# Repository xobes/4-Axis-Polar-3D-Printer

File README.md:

# 4 Axis Polar 3D Printer

This is my 4 axis, polar, "core-RΘ" 3D printer – an entirely new type of multi axis 3D printer designed from the ground up. 

Check out my [youtube video](https://www.youtube.com/watch?v=VEgwnhLHy3g) to see it in action!

### Slicer
A multi axis printer is pretty hopeless without a non-planar slicer, which is why I built this quick [radial slicer](https://github.com/jyjblrd/Radial_Non_Planar_Slicer) for the printer. This leverages the printer's rotating nozzle to print simple parts without supports, but there are some limitations to it which I cover in the YouTube video. I'm also working on an optimization based slicer which will be able to print any object without support so stay tuned for that!

### Assembly
You can view the [3d model online](https://a360.co/3VdXkRY) to see how to assemble the printer. Everything is 3D printable, however I got the extruder mount made out of metal by JLCPCB as there is quite a bit of torque on that part. I've also included the gerber files to make your own PCB buildplate, but a sheet of MDF wood would also work.

### BOM
Some links are included so you know what to get, but they are by no means the best source to get the parts.
|                          | Qty |                                                                                                                                                                                                                                                                                                                                                                                                                                | Note            |
| ------------------------ | --- | ------------------------------------------------------------------------------------------------------------------------------------------------------------------------------------------------------------------------------------------------------------------------------------------------------------------------------------------------------------------------------------------------------------------------------ | --------------- |
| Frame                    |     |                                                                                                                                                                                                                                                                                                                                                                                                                                |                 |
| 2040 Extrusion 350mm     | 1   | [Aliexpress](https://www.aliexpress.us/item/1005005037443914.html?pdp_npi=4%40dis%21USD%21US%20%244.70%21US%20%242.87%21%21%214.70%212.87%21%402101585f17218160977374631e6f09%2112000031411902085%21sh%21HK%213408833611%21X&spm=a2g0o.store_pc_allItems_or_groupList.new_all_items_2007532827729.1005005037443914&gatewayAdapt=glo2usa)                                                                                             |                 |
| 2040 Extrusion 100mm     | 1   | [Aliexpress](https://www.aliexpress.us/item/1005005037443914.html?pdp_npi=4%40dis%21USD%21US%20%244.70%21US%20%242.87%21%21%214.70%212.87%21%402101585f17218160977374631e6f09%2112000031411902085%21sh%21HK%213408833611%21X&spm=a2g0o.store_pc_allItems_or_groupList.new_all_items_2007532827729.1005005037443914&gatewayAdapt=glo2usa)                                                                                             |                 |
| 2020 Extrusion 150mm     | 1   | [Aliexpress](https://www.aliexpress.us/item/1005005037443914.html?pdp_npi=4%40dis%21USD%21US%20%244.70%21US%20%242.87%21%21%214.70%212.87%21%402101585f17218160977374631e6f09%2112000031411902085%21sh%21HK%213408833611%21X&spm=a2g0o.store_pc_allItems_or_groupList.new_all_items_2007532827729.1005005037443914&gatewayAdapt=glo2usa)                                                                                             |                 |
| 2020 Extrusion 250mm     | 1   | [Aliexpress](https://www.aliexpress.us/item/1005005037443914.html?pdp_npi=4%40dis%21USD%21US%20%244.70%21US%20%242.87%21%21%214.70%212.87%21%402101585f17218160977374631e6f09%2112000031411902085%21sh%21HK%213408833611%21X&spm=a2g0o.store_pc_allItems_or_groupList.new_all_items_2007532827729.1005005037443914&gatewayAdapt=glo2usa)                                                                                             |                 |
| 2020 corner bracket      | 10  | [Aliexpress](https://www.aliexpress.us/item/1005002883833150.html?pdp_npi=4%40dis%21USD%21US%20%248.00%21US%20%245.36%21%21%218.00%215.36%21%402101585f17218162290038619e6f09%2112000022608302408%21sh%21HK%213408833611%21X&spm=a2g0o.store_pc_allItems_or_groupList.new_all_items_2007532827729.1005002883833150&gatewayAdapt=glo2usa)                                                                                             |                 |
|                          |     |                                                                                                                                                                                                                                                                                                                                                                                                                                |                 |
| Hardware                 |     |                                                                                                                                                                                                                                                                                                                                                                                                                                |                 |
| 2020 T Nuts              | 50  | [Aliexpress](https://aliexpress.us/item/1005003023734101.html?pdp_npi=4%40dis%21USD%21US%20%243.50%21US%20%242.27%21%21%213.50%212.27%21%402101585f17218164046887395e6f09%2112000023289976894%21sh%21HK%213408833611%21X&spm=a2g0o.store_pc_allItems_or_groupList.new_all_items_2007532827729.1005003023734101&gatewayAdapt=glo2usa)                                                                                                 |                 |
| MGN9 250mm Rail          | 1   | [Aliexpress](https://www.aliexpress.us/item/1005004908405311.html?spm=a2g0o.detail.0.0.3bb48SF18SF1v1&mp=1&gatewayAdapt=glo2usa)                                                                                                                                                                                                                                                                                                     |                 |
| MGN12 250mm Rail         | 2   | [Aliexpress](https://www.aliexpress.us/item/1005004908405311.html?spm=a2g0o.detail.0.0.3bb48SF18SF1v1&mp=1&gatewayAdapt=glo2usa)                                                                                                                                                                                                                                                                                                     |                 |
| MGN9C Block              | 2   | [Aliexpress](https://www.aliexpress.us/item/1005004908405311.html?spm=a2g0o.detail.0.0.3bb48SF18SF1v1&mp=1&gatewayAdapt=glo2usa)                                                                                                                                                                                                                                                                                                     |                 |
| MGN12H Block             | 2   | [Aliexpress](https://www.aliexpress.us/item/1005004908405311.html?spm=a2g0o.detail.0.0.3bb48SF18SF1v1&mp=1&gatewayAdapt=glo2usa)                                                                                                                                                                                                                                                                                                     |                 |
| M4 Screw Set             |     | [Aliexpress](https://www.aliexpress.us/item/1005002109863123.html?spm=a2g0o.productlist.main.17.7fe82c812tBHeu&algo_pvid=9b3adcc2-eaa7-49f5-827b-65c76ebec4ab&algo_exp_id=9b3adcc2-eaa7-49f5-827b-65c76ebec4ab-8&pdp_npi=4%40dis%21USD%2114.98%218.24%21%21%2114.98%218.24%21%402101364217218106530737554e0d29%2112000018775202479%21sea%21HK%213408833611%21&curPageLogUid=3mmH5TGniEUf&utparam-url=scene%3Asearch%7Cquery_from%3A) |                 |
| M3 Screw Set             |     |                                                                                                                                                                                                                                                                                                                                                                                                                                | Need 40mm screw |
| M3 Square Nut            | 50  | [Aliexpress](https://www.aliexpress.us/item/1005001612157787.html?spm=a2g0o.productlist.main.1.5d017e8aeZHkcO&algo_pvid=3c10a105-0205-4d35-910a-e991c6a990df&algo_exp_id=3c10a105-0205-4d35-910a-e991c6a990df-0&pdp_npi=4%40dis%21USD%212.68%212.28%21%21%212.68%212.28%21%402102f6cb17218121155956718ec6aa%2112000028150283667%21sea%21HK%213408833611%21&curPageLogUid=DIoZCeJsWn29&utparam-url=scene%3Asearch%7Cquery_from%3A)    |                 |
| MR85ZZ (5x8x2.5)         | 4   | [Aliexpress](https://www.aliexpress.us/item/1005002702288640.html?pdp_npi=4%40dis%21USD%21US%20%248.00%21US%20%245.20%21%21%218.00%215.20%21%402101585f17218166743287595e6f09%2112000021776689177%21sh%21HK%213408833611%21X&spm=a2g0o.store_pc_allItems_or_groupList.new_all_items_2007532827729.1005002702288640&gatewayAdapt=glo2usa)                                                                                             | B axis          |
| 6810ZZ                   | 2   | [Aliexpress](https://www.aliexpress.us/item/32862403898.html?spm=a2g0o.productlist.main.3.28051f017e5Tbz&algo_pvid=e4d6ce69-5943-4ac6-adf3-921e6b8d509a&algo_exp_id=e4d6ce69-5943-4ac6-adf3-921e6b8d509a-1&pdp_npi=4%40dis%21USD%215.39%214.31%21%21%215.39%214.31%21%402140e84617218120288452517e1693%2165529151447%21sea%21HK%213408833611%21X&curPageLogUid=G0ytiQ8Lm1Mz&utparam-url=scene%3Asearch%7Cquery_from%3A)              | C axis          |
| 5mm Rod 50mm length      |     |                                                                                                                                                                                                                                                                                                                                                                                                                                | B axis          |
| 5mm Flange coupling      |     |                                                                                                                                                                                                                                                                                                                                                                                                                                |                 |
| 5x11x6 collet            | 1   | [Aliexpress](https://www.aliexpress.com/item/1005005687346657.html?spm=a2g0o.order_list.order_list_main.270.6df81802pwJpHi)                                                                                                                                                                                                                                                                                                          | B axis          |
|                          |     |                                                                                                                                                                                                                                                                                                                                                                                                                                |                 |
| Drive                    |     |                                                                                                                                                                                                                                                                                                                                                                                                                                |                 |
| Nema 17 300mm Lead Screw | 1   | [Aliexpress](https://www.aliexpress.us/item/1005005575285492.html?spm=a2g0o.productlist.0.0.5d017e8aeZHkcO&mp=1&gatewayAdapt=glo2usa)                                                                                                                                                                                                                                                                                                |                 |
| T8\*8 Lead Screw Nut     | 1   | [Aliexpress](https://www.aliexpress.us/item/32957828816.html?pdp_npi=3%40dis%21USD%21%21US%20%240.80%21%21%21%21%21%4021410c4117218088288495225e8dd8%21%21im%21%21&gatewayAdapt=glo2usa)                                                                                                                                                                                                                                             |                 |
| Nema 17 34mm             | 3   |                                                                                                                                                                                                                                                                                                                                                                                                                                |                 |
| GT2 Belt Loop 410mm      | 1   |                                                                                                                                                                                                                                                                                                                                                                                                                                |                 |
| GT2 Belt Loop 760mm      | 1   |                                                                                                                                                                                                                                                                                                                                                                                                                                |                 |
| GT2 Pully 16T            | 2   | [Aliexpress](https://www.aliexpress.us/item/1005004314084512.html?pdp_npi=4%40dis%21USD%21US%20%241.33%21US%20%241.13%21%21%211.33%211.13%21%402101585f17218179467507717e6f09%2112000034179345936%21sh%21HK%213408833611%21X&spm=a2g0o.store_pc_allItems_or_groupList.new_all_items_2007567262458.1005004314084512&gatewayAdapt=glo2usa)                                                                                             |                 |
| GT2 Idler 16T w/o Teeth  | 4   |                                                                                                                                                                                                                                                                                                                                                                                                                                |                 |
| GT2 Pully 40T            | 1   |                                                                                                                                                                                                                                                                                                                                                                                                                                |                 |
| GT2 Idler 16T w/ Teeth   | 2   | [Aliexpress](https://www.aliexpress.us/item/32817328238.html?spm=a2g0o.productlist.main.1.154a6eafY9AYrN&algo_pvid=2e5559f6-0e2b-4699-af66-2900a6241a77&algo_exp_id=2e5559f6-0e2b-4699-af66-2900a6241a77-0&pdp_npi=4%40dis%21USD%210.83%210.80%21%21%210.83%210.80%21%402141069c17218103868312197ecd23%2112000030774036536%21sea%21HK%213408833611%21&curPageLogUid=WzjkJAxiIMiS&utparam-url=scene%3Asearch%7Cquery_from%3A)         |                 |
|                          |     |                                                                                                                                                                                                                                                                                                                                                                                                                                |                 |
| Electronics              |     |                                                                                                                                                                                                                                                                                                                                                                                                                                |                 |
| Control Board            | 1   | [Aliexpress](https://www.aliexpress.us/item/1005002372751834.html?spm=a2g0o.cart.0.0.189e38daDy9bLj&mp=1&gatewayAdapt=glo2usa)                                                                                                                                                                                                                                                                                                       |                 |
| 24V 10A Power Brick      | 1   | [Aliexpress](https://www.aliexpress.us/item/1005003088055215.html?spm=a2g0o.productlist.main.1.274c1017SLo2cI&algo_pvid=fc15f3c2-4225-43e2-b9f1-1ec7c4a5bb77&algo_exp_id=fc15f3c2-4225-43e2-b9f1-1ec7c4a5bb77-0&pdp_npi=4%40dis%21USD%217.80%214.68%21%21%217.80%214.68%21%402102f64217218109525782817ef4f1%2112000024005691633%21sea%21HK%213408833611%21X&curPageLogUid=nAQanWwxCNH1&utparam-url=scene%3Asearch%7Cquery_from%3A)   |                 |
| 5.5x2.5 plug             | 1   | [Aliexpress](https://www.aliexpress.us/item/33034810979.html?spm=a2g0o.productlist.main.15.74b863c0UZ5tpX&algo_pvid=a17ee02e-b212-4259-a89a-ef6d215554bc&algo_exp_id=a17ee02e-b212-4259-a89a-ef6d215554bc-7&pdp_npi=4%40dis%21USD%212.00%211.76%21%21%212.00%211.76%21%402101584517218110655627764e3a68%2112000037068940694%21sea%21HK%213408833611%21&curPageLogUid=KXHREOg0VjR1&utparam-url=scene%3Asearch%7Cquery_from%3A)        |                 |
| long nozzle              | 1   | [Aliexpress](https://www.aliexpress.com/item/1005007437644929.html?spm=a2g0o.order_list.order_list_main.39.6df81802pwJpHi)                                                                                                                                                                                                                                                                                                           |                 |
| aquarium pump            | 1   | [Aliexpress](https://aliexpress.com/item/1005005987431203.html?spm=a2g0o.order_list.order_list_main.219.6df81802pwJpHi)                                                                                                                                                                                                                                                                                                              |                 |
| BIQU H2 V2S extruder     | 1   | [Aliexpress](https://www.aliexpress.com/item/1005002027842161.html?spm=a2g0o.order_list.order_list_main.274.6df81802pwJpHi)                                                                                                                                                                                                                                                                                                          |

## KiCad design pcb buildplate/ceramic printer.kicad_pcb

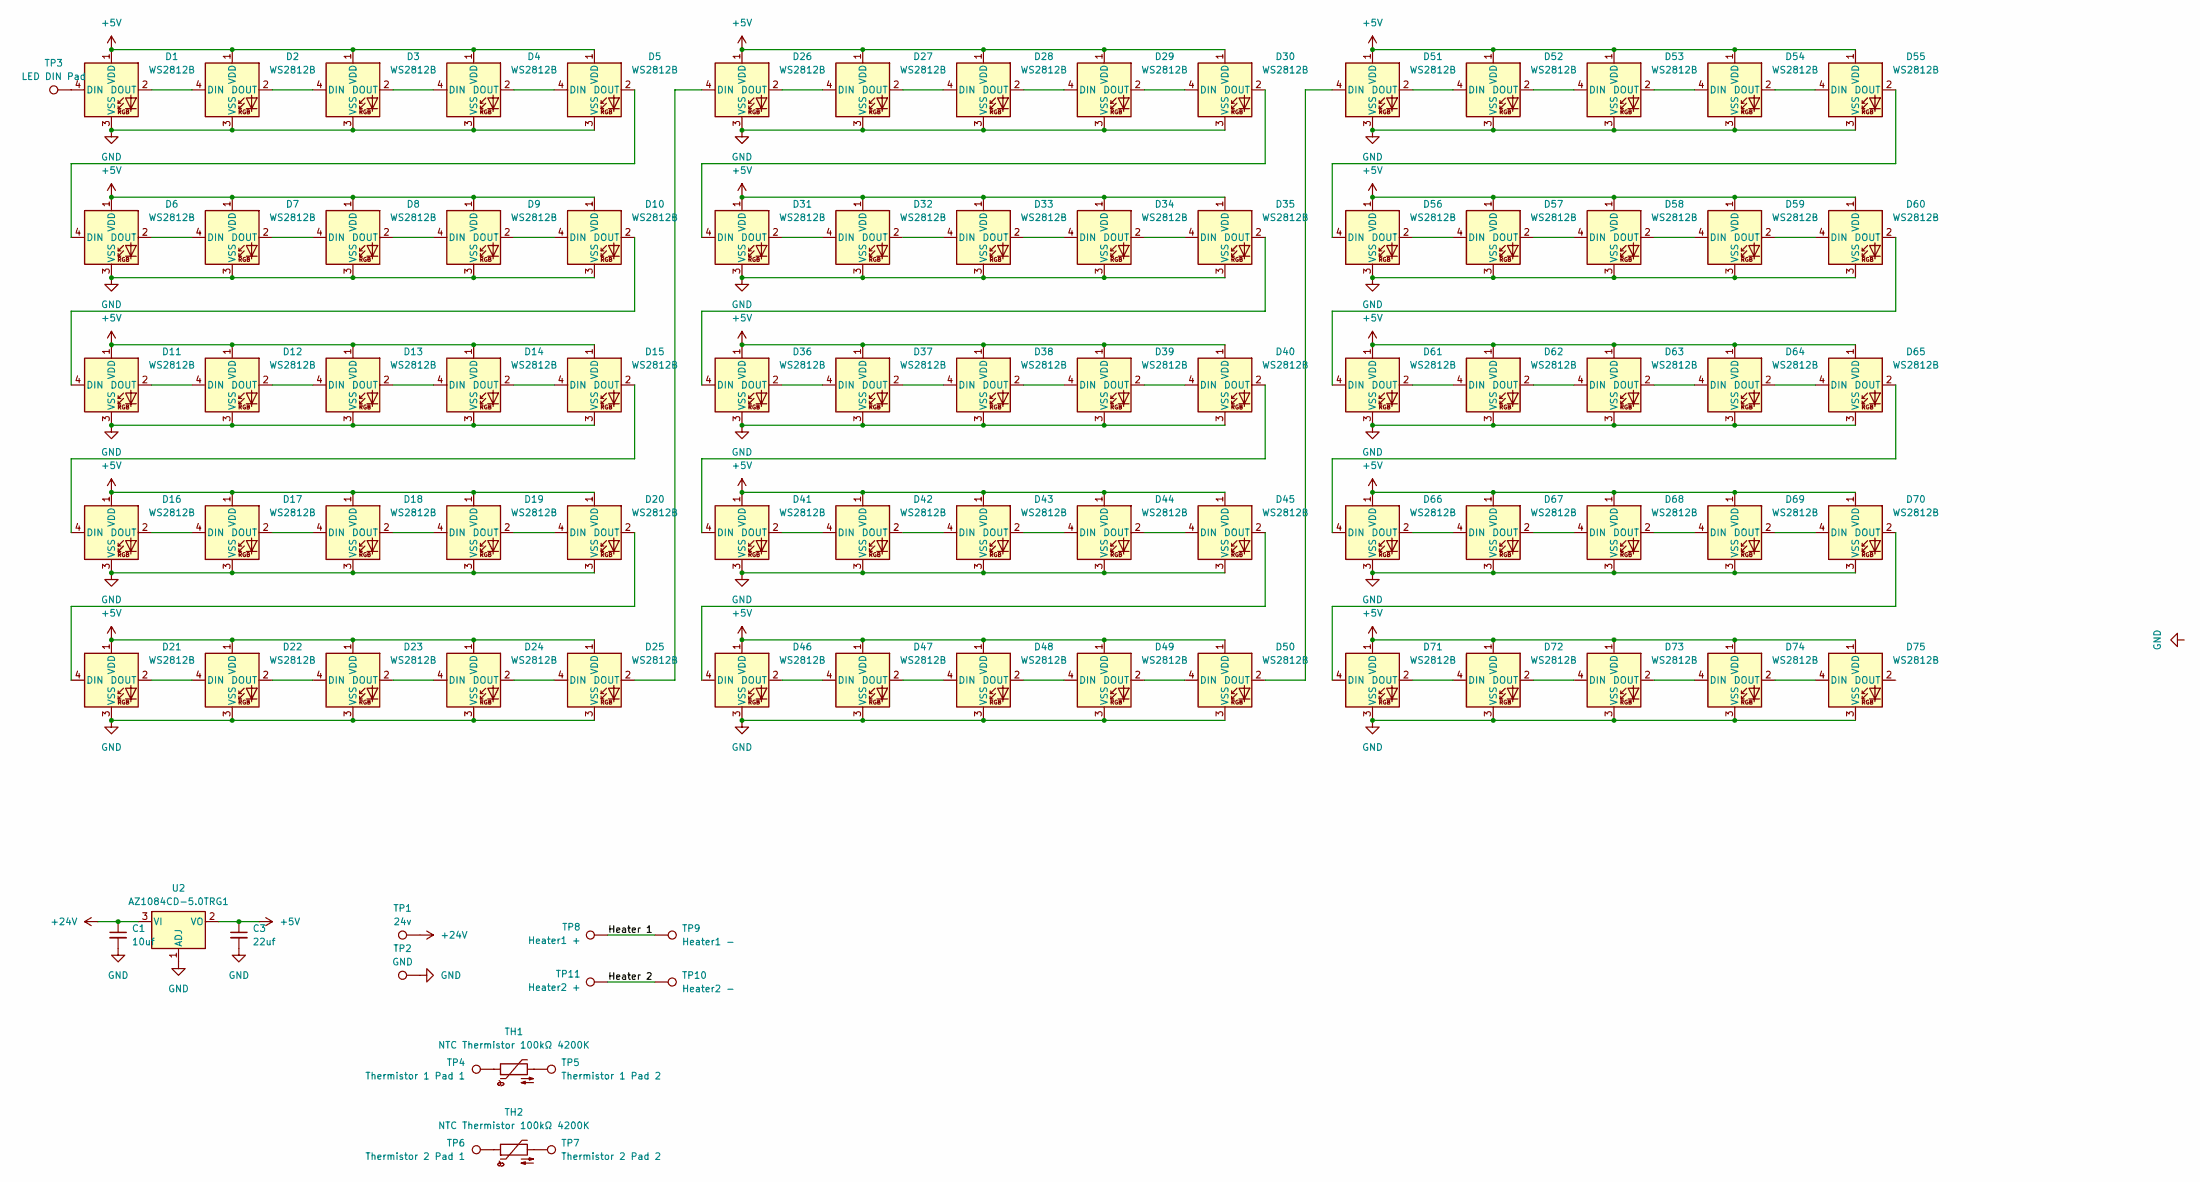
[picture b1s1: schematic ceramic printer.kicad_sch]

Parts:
C1: 10uf
C3: 22uf
D1, D2, D3, D4, D5, D6, D7, D8, D9, D10, D11, D12, D13, D14, D15, D16, D17, D18, D19, D20, D21, D22, D23, D24, D25, D26, D27, D28, D29, D30, D31, D32, D33, D34, D35, D36, D37, D38, D39, D40, D41, D42, D43, D44, D45, D46, D47, D48, D49, D50, D51, D52, D53, D54, D55, D56, D57, D58, D59, D60, D61, D62, D63, D64, D65, D66, D67, D68, D69, D70, D71, D72, D73, D74, D75: WS2812B; LED_WS2812B_PLCC4_5.0x5.0mm_P3.2mm
TH1, TH2: NTC Thermistor 100kΩ 4200K; R_0805_2012Metric_Pad1.20x1.40mm_HandSolder
TP1: 24v; TestPoint_Pad_4.0x4.0mm
TP2: GND; TestPoint_Pad_4.0x4.0mm
TP3: LED DIN Pad; TestPoint_Pad_2.5x2.5mm
TP4: Thermistor 1 Pad 1; TestPoint_Pad_2.0x2.0mm
TP5: Thermistor 1 Pad 2; TestPoint_Pad_2.0x2.0mm
TP6: Thermistor 2 Pad 1; TestPoint_Pad_2.0x2.0mm
TP7: Thermistor 2 Pad 2; TestPoint_Pad_2.0x2.0mm
TP8: Heater1 +; TestPoint_Pad_4.0x4.0mm
TP9: Heater1 -; TestPoint_Pad_4.0x4.0mm
TP10: Heater2 -; TestPoint_Pad_4.0x4.0mm
TP11: Heater2 +; TestPoint_Pad_4.0x4.0mm
U2: AZ1084CD-5.0TRG1; TO-252-2

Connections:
+5V: C3.1, D1.1 (VDD), D2.1 (VDD), D3.1 (VDD), D4.1 (VDD), D5.1 (VDD), D6.1 (VDD), D7.1 (VDD), D8.1 (VDD), D9.1 (VDD), D10.1 (VDD), D11.1 (VDD), D12.1 (VDD), D13.1 (VDD), D14.1 (VDD), D15.1 (VDD), D16.1 (VDD), D17.1 (VDD), D18.1 (VDD), D19.1 (VDD), D20.1 (VDD), D21.1 (VDD), D22.1 (VDD), D23.1 (VDD), D24.1 (VDD), D25.1 (VDD), D26.1 (VDD), D27.1 (VDD), D28.1 (VDD), D29.1 (VDD), D30.1 (VDD), D31.1 (VDD), D32.1 (VDD), D33.1 (VDD), D34.1 (VDD), D35.1 (VDD), D36.1 (VDD), D37.1 (VDD), D38.1 (VDD), D39.1 (VDD), D40.1 (VDD), D41.1 (VDD), D42.1 (VDD), D43.1 (VDD), D44.1 (VDD), D45.1 (VDD), D46.1 (VDD), D47.1 (VDD), D48.1 (VDD), D49.1 (VDD), D50.1 (VDD), D51.1 (VDD), D52.1 (VDD), D53.1 (VDD), D54.1 (VDD), D55.1 (VDD), D56.1 (VDD), D57.1 (VDD), D58.1 (VDD), D59.1 (VDD), D60.1 (VDD), D61.1 (VDD), D62.1 (VDD), D63.1 (VDD), D64.1 (VDD), D65.1 (VDD), D66.1 (VDD), D67.1 (VDD), D68.1 (VDD), D69.1 (VDD), D70.1 (VDD), D71.1 (VDD), D72.1 (VDD), D73.1 (VDD), D74.1 (VDD), D75.1 (VDD), U2.2 (VO)
+24V: C1.1, TP1.1, U2.3 (VI)
/Heater 1: TP8.1, TP9.1
/Heater 2: TP10.1, TP11.1
GND: C1.2, C3.2, D1.3 (VSS), D2.3 (VSS), D3.3 (VSS), D4.3 (VSS), D5.3 (VSS), D6.3 (VSS), D7.3 (VSS), D8.3 (VSS), D9.3 (VSS), D10.3 (VSS), D11.3 (VSS), D12.3 (VSS), D13.3 (VSS), D14.3 (VSS), D15.3 (VSS), D16.3 (VSS), D17.3 (VSS), D18.3 (VSS), D19.3 (VSS), D20.3 (VSS), D21.3 (VSS), D22.3 (VSS), D23.3 (VSS), D24.3 (VSS), D25.3 (VSS), D26.3 (VSS), D27.3 (VSS), D28.3 (VSS), D29.3 (VSS), D30.3 (VSS), D31.3 (VSS), D32.3 (VSS), D33.3 (VSS), D34.3 (VSS), D35.3 (VSS), D36.3 (VSS), D37.3 (VSS), D38.3 (VSS), D39.3 (VSS), D40.3 (VSS), D41.3 (VSS), D42.3 (VSS), D43.3 (VSS), D44.3 (VSS), D45.3 (VSS), D46.3 (VSS), D47.3 (VSS), D48.3 (VSS), D49.3 (VSS), D50.3 (VSS), D51.3 (VSS), D52.3 (VSS), D53.3 (VSS), D54.3 (VSS), D55.3 (VSS), D56.3 (VSS), D57.3 (VSS), D58.3 (VSS), D59.3 (VSS), D60.3 (VSS), D61.3 (VSS), D62.3 (VSS), D63.3 (VSS), D64.3 (VSS), D65.3 (VSS), D66.3 (VSS), D67.3 (VSS), D68.3 (VSS), D69.3 (VSS), D70.3 (VSS), D71.3 (VSS), D72.3 (VSS), D73.3 (VSS), D74.3 (VSS), D75.3 (VSS), TP2.1, U2.1 (ADJ)
unnamed: D1.4 (DIN), TP3.1
unnamed: D1.2 (DOUT), D2.4 (DIN)
unnamed: D2.2 (DOUT), D3.4 (DIN)
unnamed: D3.2 (DOUT), D4.4 (DIN)
unnamed: D4.2 (DOUT), D5.4 (DIN)
unnamed: D5.2 (DOUT), D6.4 (DIN)
unnamed: D6.2 (DOUT), D7.4 (DIN)
unnamed: D7.2 (DOUT), D8.4 (DIN)
unnamed: D8.2 (DOUT), D9.4 (DIN)
unnamed: D9.2 (DOUT), D10.4 (DIN)
unnamed: D10.2 (DOUT), D11.4 (DIN)
unnamed: D11.2 (DOUT), D12.4 (DIN)
unnamed: D12.2 (DOUT), D13.4 (DIN)
unnamed: D13.2 (DOUT), D14.4 (DIN)
unnamed: D14.2 (DOUT), D15.4 (DIN)
unnamed: D15.2 (DOUT), D16.4 (DIN)
unnamed: D16.2 (DOUT), D17.4 (DIN)
unnamed: D17.2 (DOUT), D18.4 (DIN)
unnamed: D18.2 (DOUT), D19.4 (DIN)
unnamed: D19.2 (DOUT), D20.4 (DIN)
unnamed: D20.2 (DOUT), D21.4 (DIN)
unnamed: D21.2 (DOUT), D22.4 (DIN)
unnamed: D22.2 (DOUT), D23.4 (DIN)
unnamed: D23.2 (DOUT), D24.4 (DIN)
unnamed: D24.2 (DOUT), D25.4 (DIN)
unnamed: D25.2 (DOUT), D26.4 (DIN)
unnamed: D26.2 (DOUT), D27.4 (DIN)
unnamed: D27.2 (DOUT), D28.4 (DIN)
unnamed: D28.2 (DOUT), D29.4 (DIN)
unnamed: D29.2 (DOUT), D30.4 (DIN)
unnamed: D30.2 (DOUT), D31.4 (DIN)
unnamed: D31.2 (DOUT), D32.4 (DIN)
unnamed: D32.2 (DOUT), D33.4 (DIN)
unnamed: D33.2 (DOUT), D34.4 (DIN)
unnamed: D34.2 (DOUT), D35.4 (DIN)
unnamed: D35.2 (DOUT), D36.4 (DIN)
unnamed: D36.2 (DOUT), D37.4 (DIN)
unnamed: D37.2 (DOUT), D38.4 (DIN)
unnamed: D38.2 (DOUT), D39.4 (DIN)
unnamed: D39.2 (DOUT), D40.4 (DIN)
unnamed: D40.2 (DOUT), D41.4 (DIN)
unnamed: D41.2 (DOUT), D42.4 (DIN)
unnamed: D42.2 (DOUT), D43.4 (DIN)
unnamed: D43.2 (DOUT), D44.4 (DIN)
unnamed: D44.2 (DOUT), D45.4 (DIN)
unnamed: D45.2 (DOUT), D46.4 (DIN)
unnamed: D46.2 (DOUT), D47.4 (DIN)
unnamed: D47.2 (DOUT), D48.4 (DIN)
unnamed: D48.2 (DOUT), D49.4 (DIN)
unnamed: D49.2 (DOUT), D50.4 (DIN)
unnamed: D50.2 (DOUT), D51.4 (DIN)
unnamed: D51.2 (DOUT), D52.4 (DIN)
unnamed: D52.2 (DOUT), D53.4 (DIN)
unnamed: D53.2 (DOUT), D54.4 (DIN)
unnamed: D54.2 (DOUT), D55.4 (DIN)
unnamed: D55.2 (DOUT), D56.4 (DIN)
unnamed: D56.2 (DOUT), D57.4 (DIN)
unnamed: D57.2 (DOUT), D58.4 (DIN)
unnamed: D58.2 (DOUT), D59.4 (DIN)
unnamed: D59.2 (DOUT), D60.4 (DIN)
unnamed: D60.2 (DOUT), D61.4 (DIN)
unnamed: D61.2 (DOUT), D62.4 (DIN)
unnamed: D62.2 (DOUT), D63.4 (DIN)
unnamed: D63.2 (DOUT), D64.4 (DIN)
unnamed: D64.2 (DOUT), D65.4 (DIN)
unnamed: D65.2 (DOUT), D66.4 (DIN)
unnamed: D66.2 (DOUT), D67.4 (DIN)
unnamed: D67.2 (DOUT), D68.4 (DIN)
unnamed: D68.2 (DOUT), D69.4 (DIN)
unnamed: D69.2 (DOUT), D70.4 (DIN)
unnamed: D70.2 (DOUT), D71.4 (DIN)
unnamed: D71.2 (DOUT), D72.4 (DIN)
unnamed: D72.2 (DOUT), D73.4 (DIN)
unnamed: D73.2 (DOUT), D74.4 (DIN)
unnamed: D74.2 (DOUT), D75.4 (DIN)
unnamed: TH1.1, TP4.1
unnamed: TH1.2, TP5.1
unnamed: TH2.1, TP6.1
unnamed: TH2.2, TP7.1

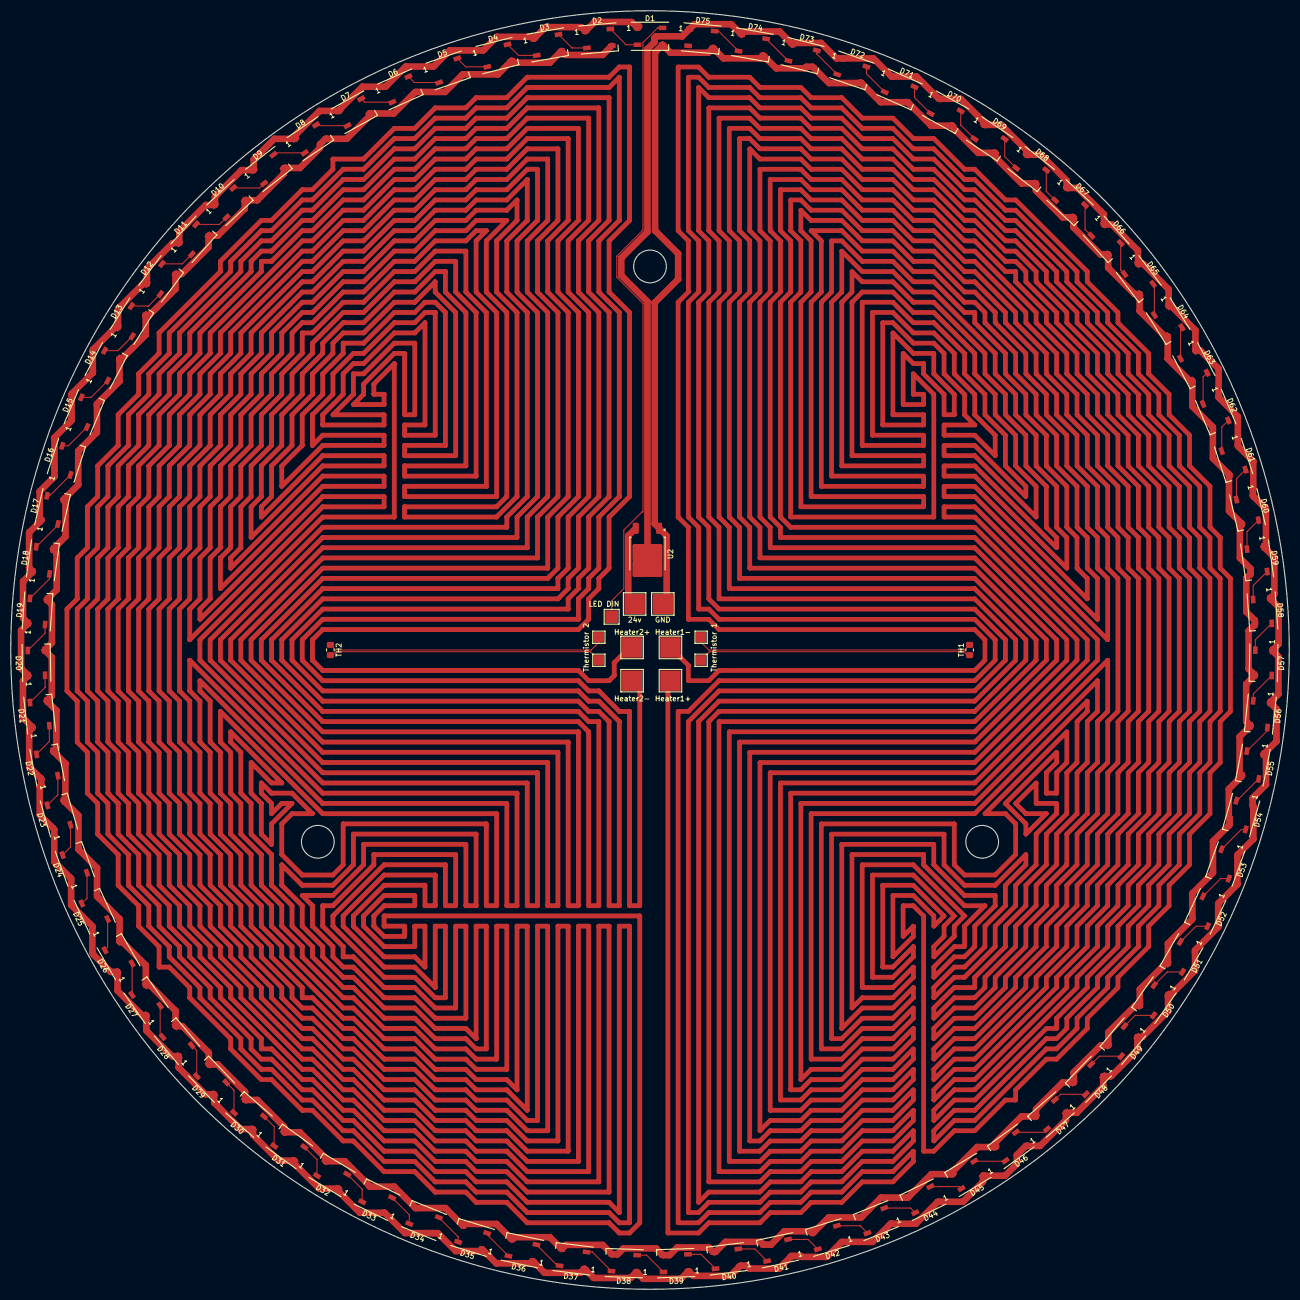
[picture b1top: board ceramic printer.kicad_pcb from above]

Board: 2 copper layers, 250.0 x 250.0 mm, 89 parts (0 on the bottom side), 84 nets.

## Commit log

2024-11-27 init
2024-12-01 Create Licence
2024-12-05 Fixed orientation of STLs to be explicit about print orientation. exported with higher poly count
2025-01-03 add rrf config
2025-01-03 add cooling duct stls
2025-01-03 more config files
2025-01-09 untested and unfinished, just to share progress
2025-01-10 tweaks based on feedback and proper modelling of extruder and set screws
2025-01-10 tweaked dimensions on slot and slider (plate) for tensioner to allow for idler pulley flanges
2025-01-10 clean up working copy
2025-01-11 added feet
2025-01-14 lots of freecad updates, z-axis modelled, working on more changes
2025-01-18 removed reference files from FreeCAD model, started modifying the cage style.
2025-01-21 Cage parted out into front, back, sides, etc. and file broken out into parts for sake of memory management.
2025-01-21 ready to move set screws...
2025-01-21 updated all copies into links for these files
2025-01-25 more work on getting things into individual files
2025-01-29 i think i got it all moved around and the cage v1 with hex pattern sorted out!
2025-02-01 added c-axis tensioner and beefier z-stop (need 2)
2025-02-06 Added electronics box (needs tweaking), and a bridge from the X/B pulleys similar to the original design
2025-02-06 adjust dimensions of the stud spacer to wrap around the bar
2025-02-17 added switch holders for limit switches, updates to 2020 bar profile, added wire slider things -- need to fix overlapp stl problem.
2025-02-17 replaced cylider with ring for goood stl
2025-02-22 freecad and stl updates, added slipring and played with some x-axis-wire-rigging, didn't work though.
2025-02-22 got homing working for my wiring/physical setup
2025-02-25 got polar version working
2025-03-01 updated electrical box to support fan, switch and have feet to connect to metal differently
